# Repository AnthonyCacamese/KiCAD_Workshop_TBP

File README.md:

# KiCAD_Workshop_TBP
This is a workshop I designed to teach PCB design skills on KiCAD to engineering students (Beginner-level).

KiCAD_Workshop_TBP.pdf Contains all necessary information for facilitating the session. 

The workshop includes a conceptual introduction to Symbols, Schematics, Footprints, and PCB Layout Design and exporting.
Participants are walked through creating a project from scratch, using the KiCAD digital library, placing and arranging symbols in a schematic, assigning footprints to symbols, and translating the schematic into a practical and personalized board design.

Importing symbol, footprint, and step files to build a custom parts library is outside of this workshop's scope. Thus, it relies only on parts found within KiCAD's default library.

At the end of the workshop, participants should be able to navigate KiCAD confidently and design simple PCBs on their own.

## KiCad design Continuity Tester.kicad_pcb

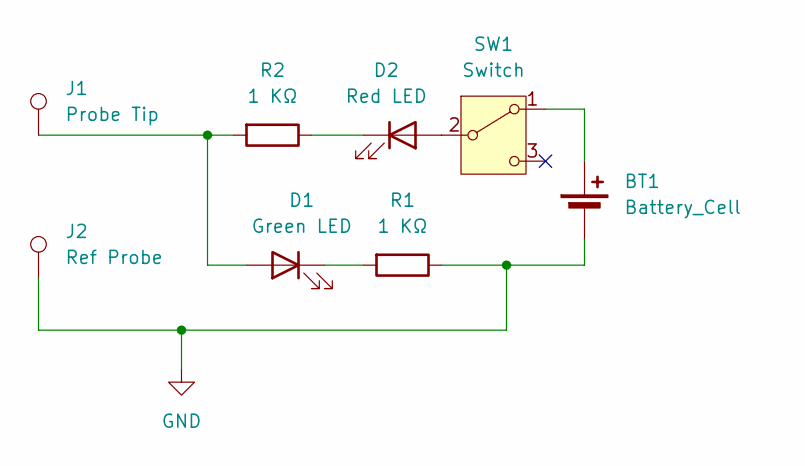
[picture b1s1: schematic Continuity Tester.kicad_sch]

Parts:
BT1: Battery_Cell; BatteryHolder_Keystone_1058_1x2032
D1: Green LED; LED_D5.0mm
D2: Red LED; LED_D5.0mm
J1: Probe Tip; TestPoint_Pad_D2.0mm
J2: Ref Probe; TestPoint_Pad_D2.0mm
R1, R2: 1 KΩ; R_Axial_DIN0207_L6.3mm_D2.5mm_P7.62mm_Horizontal
SW1: Switch; SW_Slide-03_Wuerth-WS-SLTV_10x2.5x6.4_P2.54mm

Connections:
GND: BT1.2 (-), J2.1 (1_1), R1.1
unnamed: BT1.1 (+), SW1.1 (A)
unnamed: D1.2 (A), J1.1 (1_1), R2.2
unnamed: D1.1 (K), R1.2
unnamed: D2.2 (A), SW1.2 (B)
unnamed: D2.1 (K), R2.1

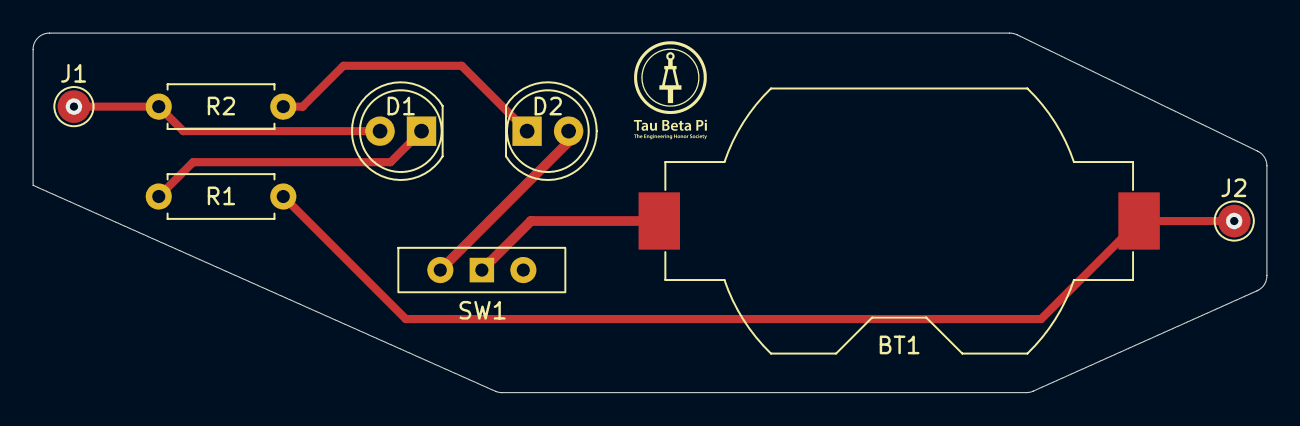
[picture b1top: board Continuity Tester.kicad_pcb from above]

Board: 2 copper layers, 75.5 x 22.0 mm, 8 parts (0 on the bottom side), 6 nets.
